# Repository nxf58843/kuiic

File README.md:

# KUIIC

## K32L2B USB to IIC Kit

This board is a tiny USB to Qwiic development board in a bread-board friendly DIP form factor.  In addition to micro USB and Qwiic connectors, it also has a reset button, RGB LED, and footprint for SPI flash expansion on the back of the board.  The pinout and form factor are designed to be compatible with the Seeeduino XIAO board.  The MCU is an NXP K32L2B Arm Cortex-M0+ with crystal-less USB and integrated VBUS to 3V regulator.  

## Software Support

This board is currently supported by the open source [TinyUSB](https://docs.tinyusb.org/en/latest/) and Adafruit's [TinyUF2](https://github.com/adafruit/tinyuf2) to enable drag-n-drop firmware updates.

## Board Design Files
The KiCad source files are included in this repository along with a [pdf copy of the schematic](out/kuiic.pdf).

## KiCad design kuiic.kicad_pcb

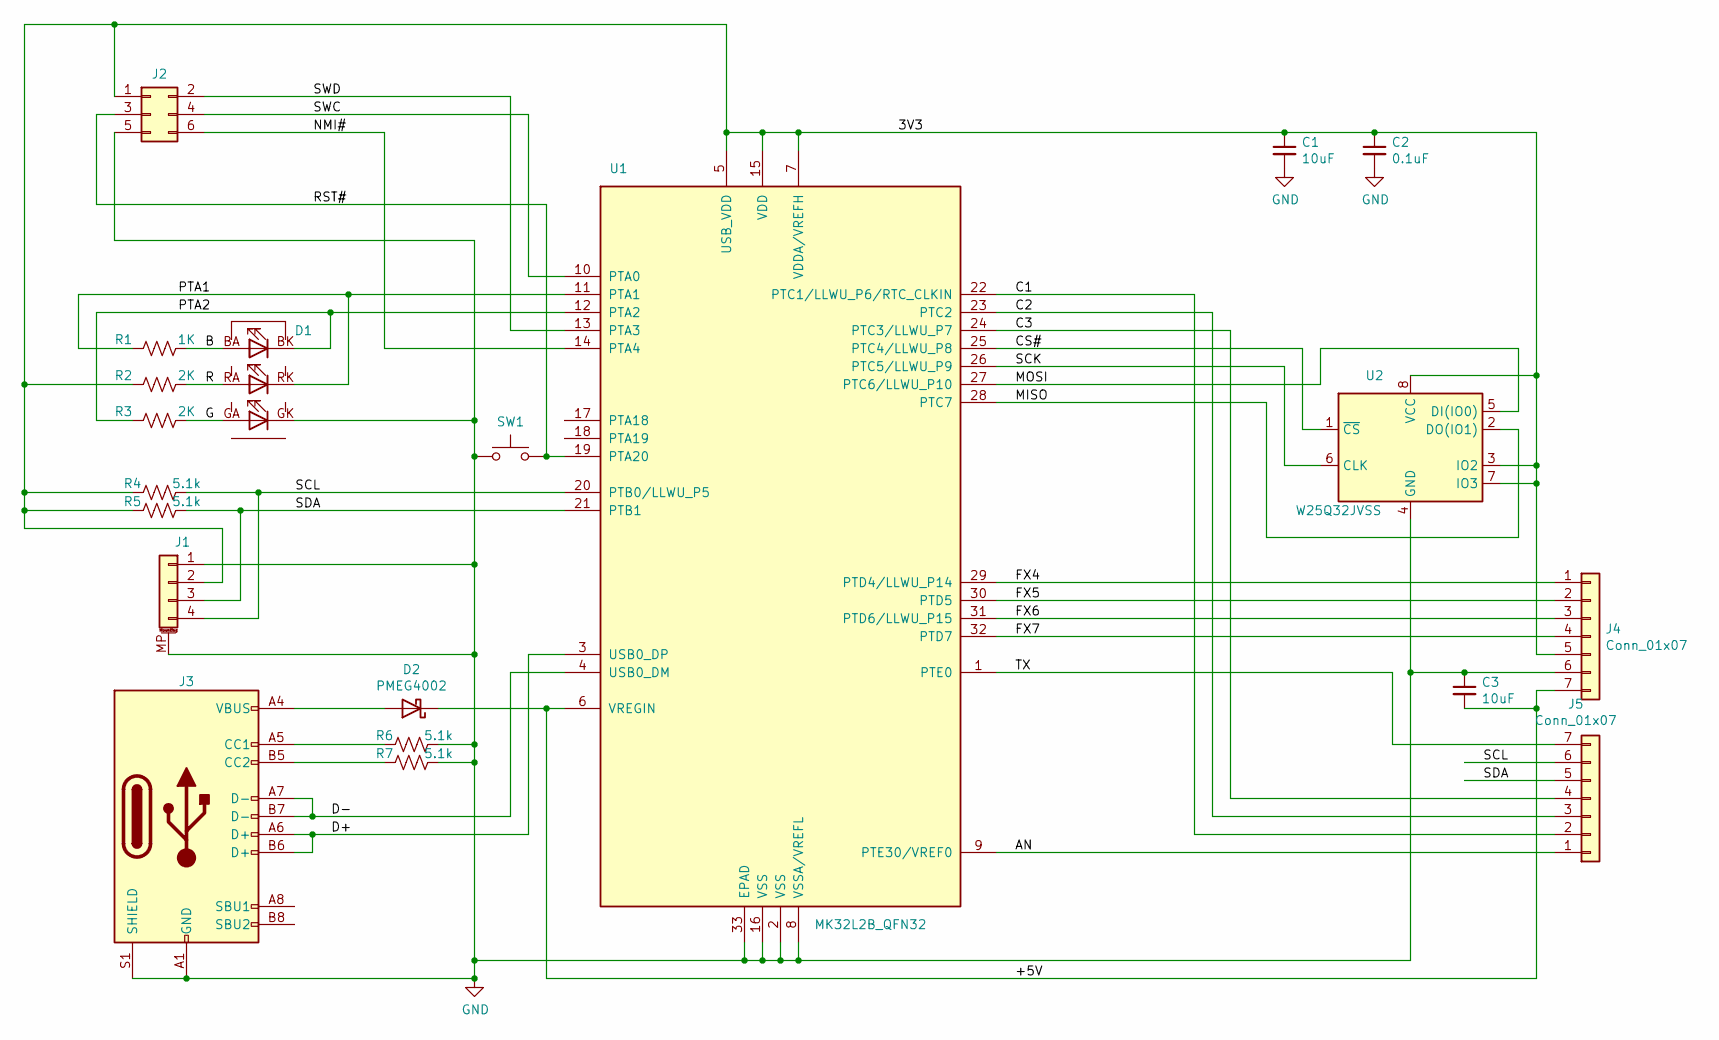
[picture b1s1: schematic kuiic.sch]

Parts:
C1, C3: 10uF; C_0603_1608Metric; MPN CL10A106KP8NNNC
C2: 0.1uF; C_0402_1005Metric; MPN CC0402KRX7R7BB104
D1: LED_RGB; LED_E6C1615; MPN E6C1615RGBC3UDA
D2: PMEG4002; D_SOD-882; MPN pmeg3005el
J1: Conn_01x04_MountingPin; QWIIC; MPN SM04B-SRSS-TB
J2: Conn_02x03_Odd_Even; Tag-Connect_TC2030-IDC-NL_2x03_P1.27mm_Vertical; MPN DNP
J3: USB_C_Receptacle_USB2.0; USB_C_Receptacle_XKB_U262-16XN-4BVC11; MPN U262-161N-4BVC11
J4, J5: Conn_01x07; PinHeader_1x07_P2.54mm_castle; MPN DNP
R1: 1K; R_0402_1005Metric; MPN RC0402JR-071KL
R2, R3: 2K; R_0402_1005Metric; MPN RC0402JR-072KL
R4, R5, R6, R7: 5.1k; R_0402_1005Metric; MPN RC0402JR-075K1L
SW1: SW_Push; SW_Push_4pin_3.0x3.65mm; MPN TS342A4P-WZ
U1: MK32L2B_QFN32; QFN-32-1EP_5x5mm_P0.5mm_EP3.45x3.45mm; MPN K32L2B31VFM0A
U2: W25Q32JVSS; SOIC-8_5.23x5.23mm_P1.27mm; MPN DNP

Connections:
/3V3: C1.1, C2.1, J1.2, J2.1, J4.5, R2.2, R4.2, R5.2, U1.5 (USB_VDD), U1.7 (VDDA/VREFH), U1.15 (VDD), U2.3 (IO2), U2.7 (IO3), U2.8 (VCC)
/+5V: C3.2, D2.1 (K), J4.7, U1.6 (VREGIN)
/AN: J5.1, U1.9 (PTE30/VREF0)
/B: D1.BA, R1.1
/C1: J5.2, U1.22 (PTC1/LLWU_P6/RTC_CLKIN)
/C2: J5.3, U1.23 (PTC2)
/C3: J5.4, U1.24 (PTC3/LLWU_P7)
/CS#: U1.25 (PTC4/LLWU_P8), U2.1 (~CS)
/D+: J3.A6 (D+), J3.B6 (D+), U1.3 (USB0_DP)
/D-: J3.A7 (D-), J3.B7 (D-), U1.4 (USB0_DM)
/FX4: J4.1, U1.29 (PTD4/LLWU_P14)
/FX5: J4.2, U1.30 (PTD5)
/FX6: J4.3, U1.31 (PTD6/LLWU_P15)
/FX7: J4.4, U1.32 (PTD7)
/G: D1.GA, R3.1
/MISO: U1.28 (PTC7), U2.2 (DO(IO1))
/MOSI: U1.27 (PTC6/LLWU_P10), U2.5 (DI(IO0))
/NMI#: J2.6, U1.14 (PTA4)
/PTA1: D1.RK, R1.2, U1.11 (PTA1)
/PTA2: D1.BK, R3.2, U1.12 (PTA2)
/R: D1.RA, R2.1
/RST#: J2.3, SW1.2, U1.19 (PTA20)
/SCK: U1.26 (PTC5/LLWU_P9), U2.6 (CLK)
/SCL: J1.4, J5.6, R4.1, U1.20 (PTB0/LLWU_P5)
/SDA: J1.3, J5.5, R5.1, U1.21 (PTB1)
/SWC: J2.4, U1.10 (PTA0)
/SWD: J2.2, U1.13 (PTA3)
/TX: J5.7, U1.1 (PTE0)
GND: C1.2, C2.2, C3.1, D1.GK, J1.1, J1.MP (MountPin), J2.5, J3.A1 (GND), J3.A12 (GND), J3.B1 (GND), J3.B12 (GND), J3.S1 (SHIELD), J4.6, R6.1, R7.1, SW1.1, U1.2 (VSS), U1.8 (VSSA/VREFL), U1.16 (VSS), U1.33 (EPAD), U2.4 (GND)
unnamed: D2.2 (A), J3.A4 (VBUS), J3.A9 (VBUS), J3.B4 (VBUS), J3.B9 (VBUS)
unnamed: J3.A5 (CC1), R6.2
unnamed: J3.B5 (CC2), R7.2

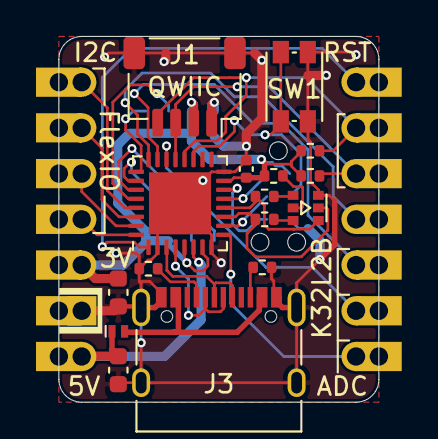
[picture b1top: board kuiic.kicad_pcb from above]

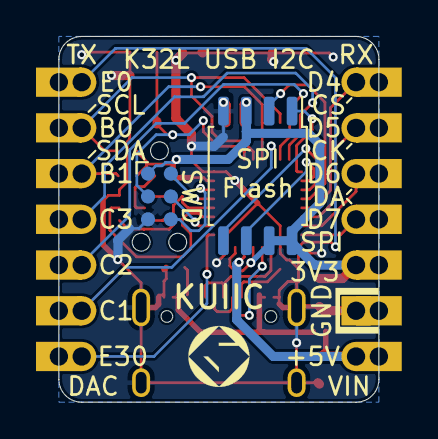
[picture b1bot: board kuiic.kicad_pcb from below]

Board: 2 copper layers, 17.8 x 20.3 mm, 20 parts (2 on the bottom side), 32 nets.

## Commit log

2021-02-23 initial commit with compplete design
2021-02-23 More alternate functions, better tag connect
2021-02-23 Cleaned up back side pinouts
2021-02-25 reorg and new flex rainbow
2021-02-26 flexio pin colors
2021-03-01 extended pads to edge of board
2021-03-30 added pinout diagram
2021-04-06 added high level description
2021-04-06 fixed title
2021-05-10 Condensed ADC inputs and MOSI/MSIO
2021-12-15 updated readme and pinout diagram
2021-12-15 updated pinout diagram
2021-12-15 added link to schematic to readme
